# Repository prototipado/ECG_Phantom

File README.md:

# Fantoma ECG

Simulador y calibrador de señales electrocardíacas multicanal. Este proyecto integra el diseño de hardware analógico/digital, simulaciones de filtrado en LTSpice, implementaciones de firmware para RP2040 y RP2350, y software de control en Python.

## Arquitectura del sistema

```mermaid
flowchart TD
    subgraph HW["Hardware y Señal"]
        MCU["RP2040 / RP2350<br/>(Raspberry Pi Pico)"]
        FILT["Filtros Reconstrucción PWM/DAC<br/>(Simulados en LTSpice)"]
        OUT["Salida 9-12 Derivaciones ECG + PPG"]
        MCU --> FILT --> OUT
    end
    subgraph FW["Firmware"]
        FW1["01. Reproductor Clínico (Flash/PhysioNet)"]
        FW2["02. Modelo Conducción (VdP + FHN)"]
        FW3["03. Síntesis Gaussiana + PPG"]
        FW4["04. Multi-Modelo 4-en-1"]
        FW5["05. Simulador Marcapasos (Pacer)"]
    end
    FW -.->|Carga según aplicación| MCU
    subgraph SW["Software Host"]
        PY["ecg_gui.py (Python)"]
        PLOT["Monitoreo multicanal en tiempo real"]
        CFG["Configuración de parámetros"]
        PY --> PLOT
        PY --> CFG
    end
    MCU <== "Streaming Serie USB (Handshake binario / 2000 SPS)" ==> PY
```

## Estructura del repositorio

* [`hardware/`](./hardware/): Proyecto KiCad (`pico_ecg`), esquemáticos, PCB, huellas, modelos 3D, Gerber y BOM.
* [`simulaciones/`](./simulaciones/): Circuitos LTSpice para filtrado analógico (PWM a voltaje), detección de impulsos y scripts en Python.
* [`firmware/`](./firmware/): Código para Raspberry Pi Pico y Pico 2:
  * [`01_pico_ecg`](./firmware/01_pico_ecg/): Reproductor de registros clínicos guardados en memoria Flash.
  * [`02_pico_conduction_model`](./firmware/02_pico_conduction_model/): Modelo biofísico de conducción cardíaca (Van der Pol + FitzHugh-Nagumo, 12 derivaciones).
  * [`03_pico_ecg_gaussian_ppg`](./firmware/03_pico_ecg_gaussian_ppg/): Síntesis analítica evento-driven (kernels Gaussianos) de ECG 12 derivaciones + pulso óptico PPG.
  * Módulos avanzados en desarrollo (`04_pico_multimodel` y `05_pace_sim_intracardiac_9_nodes`).
* [`software/`](./software/): Interfaz de escritorio en Python para visualización multicanal, registro de datos y control remoto.
* [`datasets/`](./datasets/): Registros de bases clínicas (PhysioNet, LUDB) y scripts para convertirlos a arreglos en C (`.h`).
* [`docs/`](./docs/): Protocolo de comunicación, referencias bibliográficas y notas de diseño.

## Características

* Salida de derivaciones estándar (I, II, III, aVR, aVL, aVF, V1-V6) y canal auxiliar PPG.
* Generación analógica a electrodos y transmisión serie por USB (hasta 2000 SPS).
* Control local mediante menú en pantalla OLED y encoder rotativo, o remoto desde la GUI en Python.
* Simulación de ritmos normales y patologías (taquicardia, bradicardia, fibrilación, bloqueos AV, deriva de línea base).

## Inicio rápido

### Dependencias de software (GUI)

```bash
cd software
python -m venv .venv

# En Windows:
.venv\Scripts\activate

# En Linux/macOS:
source .venv/bin/activate

pip install -r requirements.txt
python ecg_gui.py
```

### Carga de firmware

1. Navegar a la carpeta del firmware deseado (por ejemplo, [`firmware/01_pico_ecg/`](./firmware/01_pico_ecg/)).
2. Conectar la Raspberry Pi Pico manteniendo presionado el botón BOOTSEL.
3. Copiar el archivo `.uf2` compilado a la unidad USB generada.

## Estado del desarrollo

- [x] Caracterización y simulación de filtros pasa-bajos en LTSpice.
- [x] Firmware base `01_pico_ecg` para reproducción de registros clínicos.
- [x] Firmware `02_pico_conduction_model` (modelo electrofisiológico VdP + FHN).
- [x] Firmware `03_pico_ecg_gaussian_ppg` (síntesis Gaussiana ECG de 12 derivaciones + pulso óptico PPG).
- [ ] Suite de firmwares avanzados (`04_pico_multimodel` y `05_pace_sim_intracardiac_9_nodes`).
- [x] Diseños finales de PCB y acondicionamiento de señal en KiCad.
- [x] GUI en Python para captura en tiempo real, registro a CSV y compilación a ejecutable.

## Licencia

Este proyecto está bajo la Licencia MIT. Ver el archivo [`LICENSE`](./LICENSE) para más detalles.

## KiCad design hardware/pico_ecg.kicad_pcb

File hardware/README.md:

# Diseño de Hardware (KiCad)

Este directorio contiene el diseño electrónico y mecánico del Fantoma ECG, organizado como un proyecto unificado en KiCad.

## Estructura del proyecto

### Archivos de diseño KiCad

- **`pico_ecg.kicad_pro`**: Archivo principal del proyecto KiCad.
- **`pico_ecg.kicad_sch`**: Esquema de circuito principal (etapa analógica, microcontrolador y conectores).
- **`filtros.kicad_sch`**: Sub-esquema de la etapa de filtrado analógico.
- **`pacemaker.kicad_sch`**: Sub-esquema del simulador de marcapasos.
- **`pico_ecg.kicad_pcb`**: Ruteo de la placa de circuito impreso (PCB).

### Directorios

- **`pico_ecg.pretty/`**: Librería de huellas (footprints) locales utilizadas en el diseño — incluye huellas para OLED, Raspberry Pi Pico, cargador TP4056, encoder rotativo, entre otros.
- **`3d_models/`**: Modelos 3D de componentes (STEP/WRL) para visualización en KiCad — incluye Raspberry Pi Pico, OLED 0.96", cargador LiPo, encoder rotativo, y el ensamblaje completo (`pico_ecg.step`).
- **`case/`**: Archivos STL para impresión 3D del gabinete del dispositivo (`base.stl`, `frente.stl`) y fotografías del ensamblaje.
- **`gerber/`**: Archivos de fabricación (Gerber) y de perforación (Drill) listos para enviar a fabricación.
- **`bom/`**: Lista de materiales (`pico_ecg_BOM.csv`) con referencias de componentes, valores y huellas.
- **`docs/`**: Esquemático exportado en PDF (`pico_ecg.pdf`) para revisión rápida sin necesidad de KiCad.
- **`images/`**: Renderizados de la PCB y esquemas de filtrado.

## Imágenes

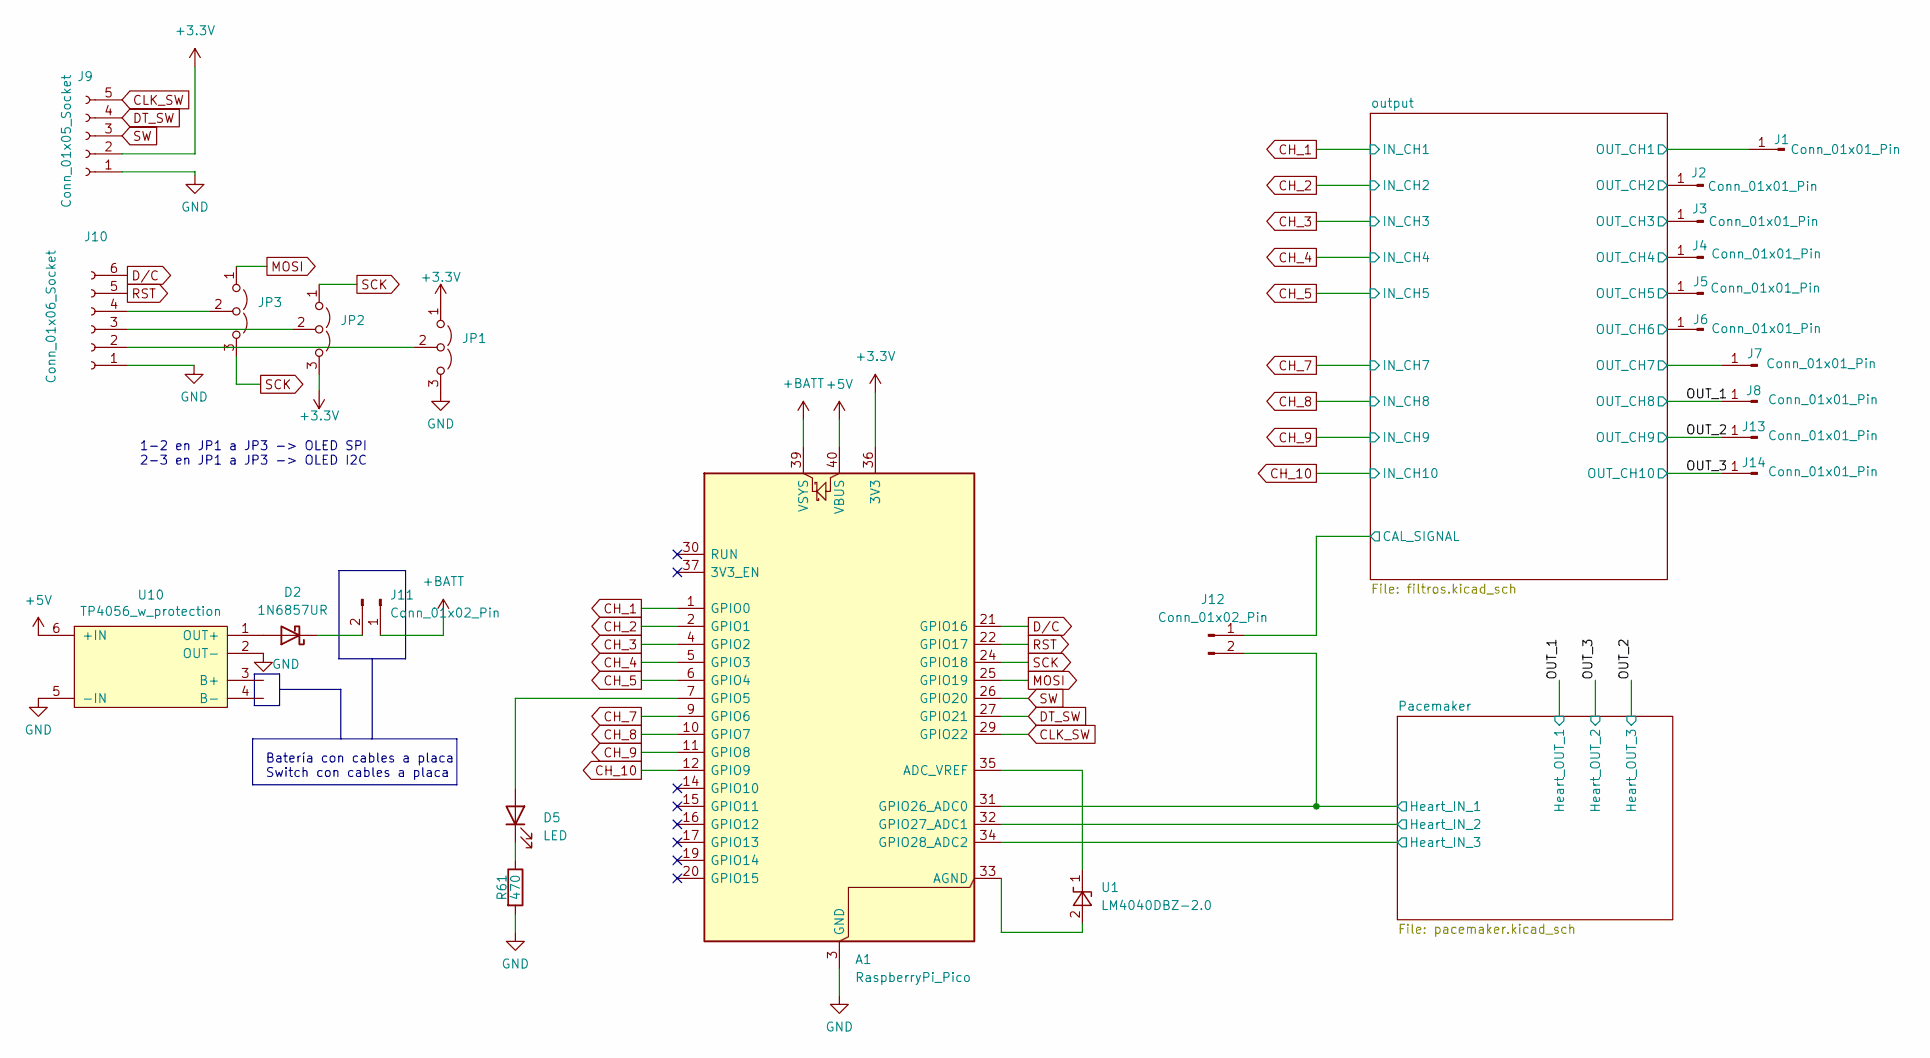
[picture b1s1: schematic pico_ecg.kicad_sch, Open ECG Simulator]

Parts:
A1: RaspberryPi_Pico; RaspberryPi_Pico_Common_Unspecified; Manufacturer PN SC1631
D2: 1N6857UR; D_MELF
D5: LED; LED_0805_2012Metric; Manufacturer PN 160-1427-1-ND
J1, J2, J3, J4, J5, J6, J7, J8, J13, J14: Conn_01x01_Pin; Pin_D1.4mm_L8.5mm_W2.8mm_FlatFork
J9: Conn_01x05_Socket; PinSocket_1x05_P2.54mm_Vertical
J10: Conn_01x06_Socket; PinSocket_1x06_P2.54mm_Vertical
J11, J12: Conn_01x02_Pin; PinHeader_1x02_P2.54mm_Vertical
JP1, JP2, JP3: Jumper_3_Open; SolderJumper-3_P1.3mm_Open_RoundedPad1.0x1.5mm
R61: 470; R_0603_1608Metric_Pad0.98x0.95mm_HandSolder; Manufacturer PN RC0603JR-07470RL
U1: LM4040DBZ-2.0; SOT-23; Manufacturer PN LM4040CIM3-2.0/NOPB
U10: TP4056_w_protection

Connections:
+3.3V: A1.36 (3V3), J9.2, JP1.1 (A), JP2.3 (B); also elsewhere on the board
+5V: A1.40 (VBUS), U10.6 (+IN)
+BATT: A1.39 (VSYS), J11.1
/OUT_1: J8.1 (Pin_1_1); also elsewhere on the board
/OUT_2: J13.1 (Pin_1_1); also elsewhere on the board
/OUT_3: J14.1 (Pin_1_1); also elsewhere on the board
/Pacemaker/Heart_IN_1: A1.31 (GPIO26_ADC0), J12.2; also elsewhere on the board
/Pacemaker/Heart_IN_2: A1.32 (GPIO27_ADC1); also elsewhere on the board
/Pacemaker/Heart_IN_3: A1.34 (GPIO28_ADC2); also elsewhere on the board
/output/CAL_SIGNAL: J12.1; also elsewhere on the board
/output/OUT_CH1: J1.1 (Pin_1_1); also elsewhere on the board
/output/OUT_CH2: J2.1 (Pin_1_1); also elsewhere on the board
/output/OUT_CH3: J3.1 (Pin_1_1); also elsewhere on the board
/output/OUT_CH4: J4.1 (Pin_1_1); also elsewhere on the board
/output/OUT_CH5: J5.1 (Pin_1_1); also elsewhere on the board
/output/OUT_CH6: J6.1 (Pin_1_1); also elsewhere on the board
/output/OUT_CH7: J7.1 (Pin_1_1); also elsewhere on the board
CH_1: A1.1 (GPIO0); also elsewhere on the board
CH_2: A1.2 (GPIO1); also elsewhere on the board
CH_3: A1.4 (GPIO2); also elsewhere on the board
CH_4: A1.5 (GPIO3); also elsewhere on the board
CH_5: A1.6 (GPIO4); also elsewhere on the board
CH_7: A1.9 (GPIO6); also elsewhere on the board
CH_8: A1.10 (GPIO7); also elsewhere on the board
CH_9: A1.11 (GPIO8); also elsewhere on the board
CH_10: A1.12 (GPIO9); also elsewhere on the board
CLK_SW: A1.29 (GPIO22), J9.5
DT_SW: A1.27 (GPIO21), J9.4
D/C: A1.21 (GPIO16), J10.6
GND: A1.3 (GND), A1.8 (GND), A1.13 (GND), A1.18 (GND), A1.23 (GND), A1.28 (GND), A1.38 (GND), J9.1, J10.1, JP1.3 (B), R61.2, U10.2 (OUT-), U10.5 (-IN); also elsewhere on the board
MOSI: A1.25 (GPIO19), JP3.1 (A)
unnamed: A1.35 (ADC_VREF), U1.1 (K)
unnamed: A1.33 (AGND), U1.2 (A)
unnamed: A1.7 (GPIO5), D5.2 (A)
unnamed: D2.2 (A), U10.1 (OUT+)
unnamed: D2.1 (K), J11.2
unnamed: D5.1 (K), R61.1
unnamed: J10.2, JP1.2 (C)
unnamed: J10.3, JP2.2 (C)
unnamed: J10.4, JP3.2 (C)
RST: A1.22 (GPIO17), J10.5
SCK: A1.24 (GPIO18), JP2.1 (A), JP3.3 (B)
SW: A1.26 (GPIO20), J9.3

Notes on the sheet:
1-2 en JP1 a JP3 -> OLED SPI 2-3 en JP1 a JP3 -> OLED I2C
Batería con cables a placa Switch con cables a placa

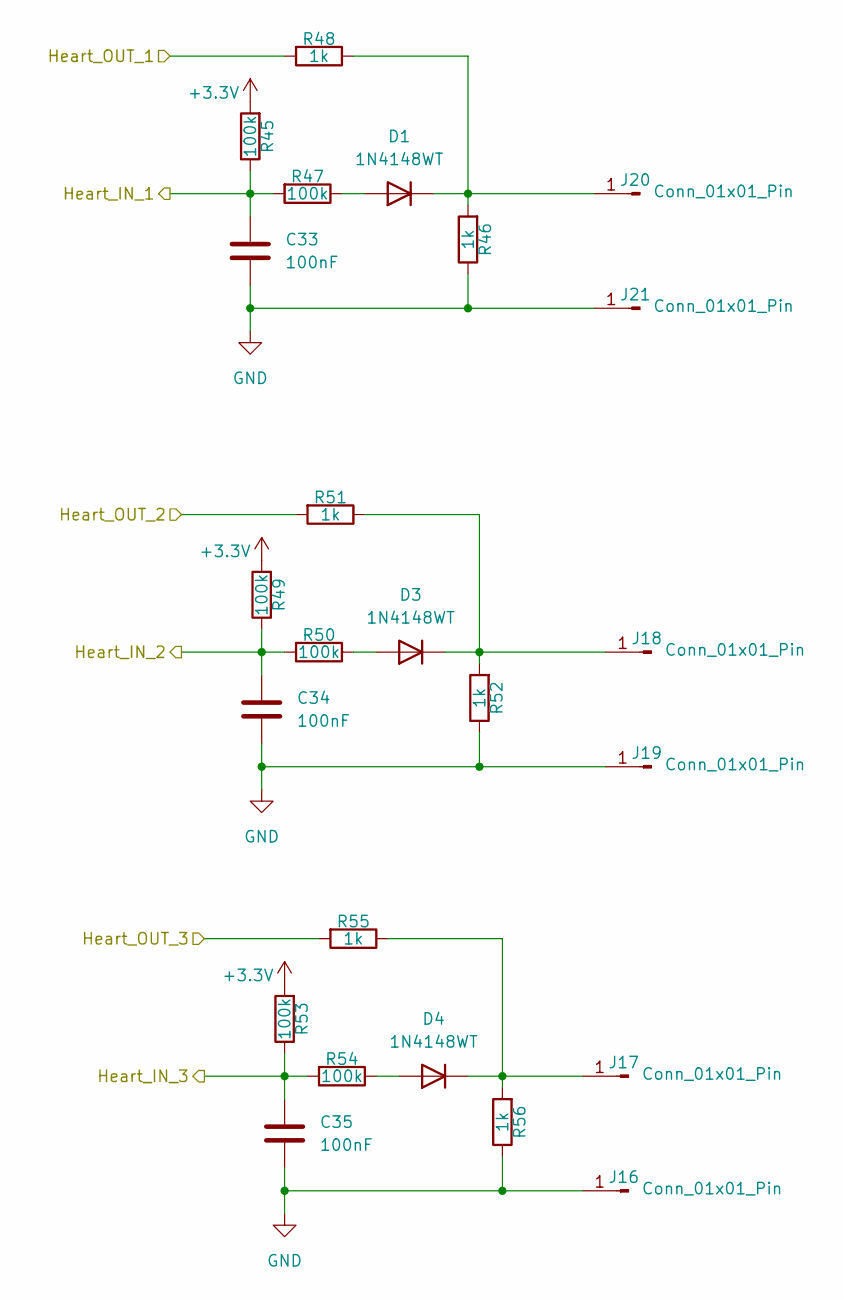
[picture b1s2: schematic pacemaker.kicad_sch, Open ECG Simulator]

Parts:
C33, C34, C35: 100nF; C_0603_1608Metric_Pad1.08x0.95mm_HandSolder; Manufacturer PN C0603C104K5RACTU
D1, D3, D4: 1N4148WT; D_SOD-523; Manufacturer PN 1N4148WT-7
J16, J17, J18, J19, J20, J21: Conn_01x01_Pin; Pin_D1.4mm_L8.5mm_W2.8mm_FlatFork
R45, R47, R49, R50, R53, R54: 100k; R_0603_1608Metric_Pad0.98x0.95mm_HandSolder; Manufacturer PN RC0603JR-07100KL
R46, R48, R51, R52, R55, R56: 1k; R_0603_1608Metric_Pad0.98x0.95mm_HandSolder; Manufacturer PN RC0603JR-071KL

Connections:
+3.3V: R45.2, R49.2, R53.2; also elsewhere on the board
/OUT_1: R48.2; also elsewhere on the board
/OUT_2: R55.2; also elsewhere on the board
/OUT_3: R51.2; also elsewhere on the board
/Pacemaker/Heart_IN_1: C33.2, R45.1, R47.2; also elsewhere on the board
/Pacemaker/Heart_IN_2: C34.2, R49.1, R50.2; also elsewhere on the board
/Pacemaker/Heart_IN_3: C35.2, R53.1, R54.2; also elsewhere on the board
GND: C33.1, C34.1, C35.1, J16.1 (Pin_1_1), J19.1 (Pin_1_1), J21.1 (Pin_1_1), R46.1, R52.1, R56.1; also elsewhere on the board
unnamed: D1.2 (A), R47.1
unnamed: D1.1 (K), J20.1 (Pin_1_1), R46.2, R48.1
unnamed: D3.2 (A), R50.1
unnamed: D3.1 (K), J18.1 (Pin_1_1), R51.1, R52.2
unnamed: D4.2 (A), R54.1
unnamed: D4.1 (K), J17.1 (Pin_1_1), R55.1, R56.2

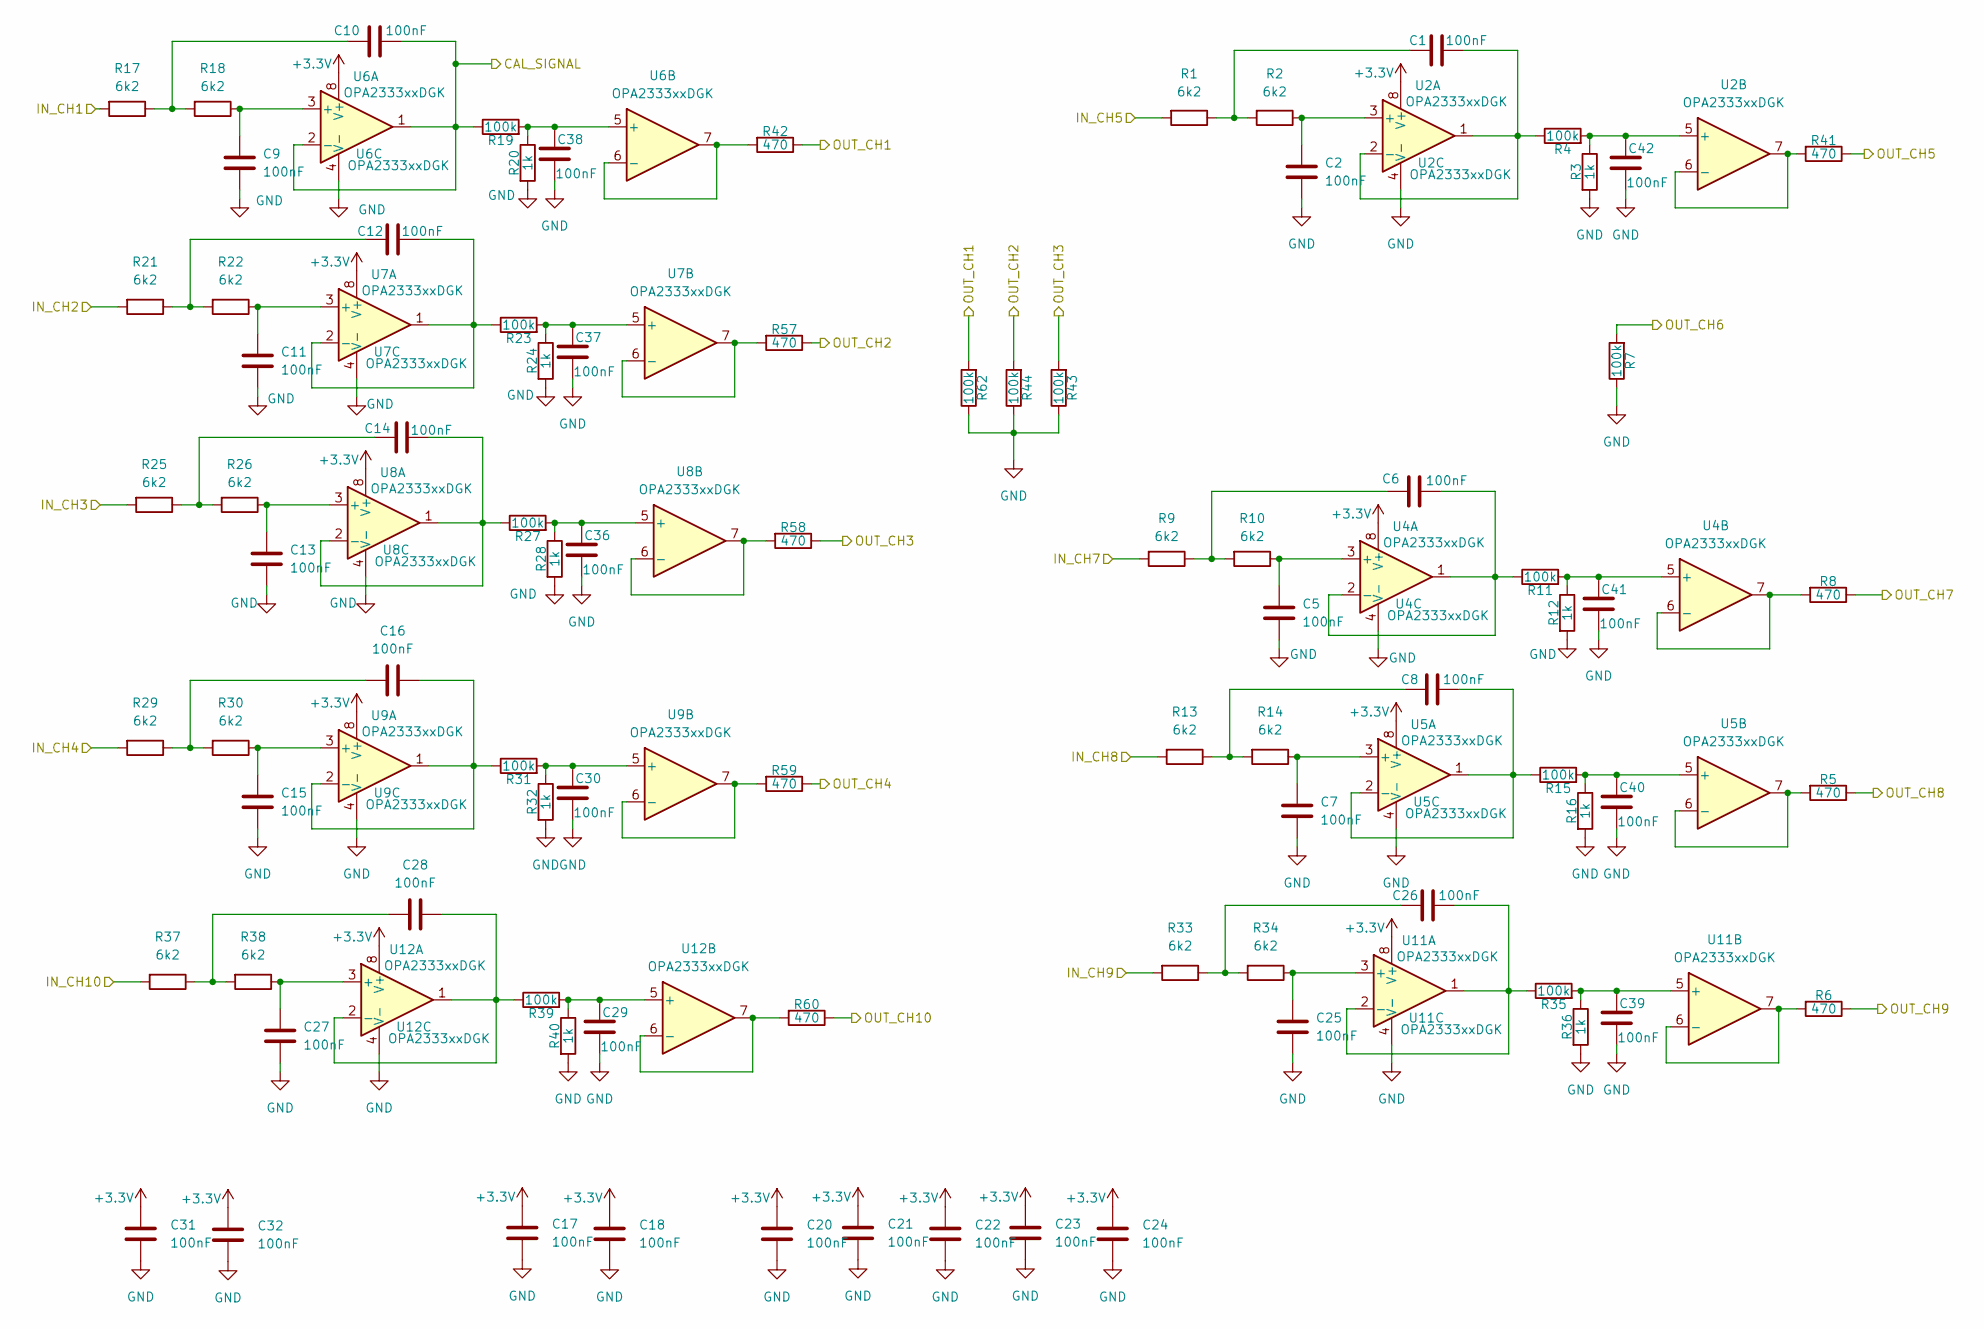
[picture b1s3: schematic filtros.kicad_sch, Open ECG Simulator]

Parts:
C1, C2, C5, C6, C7, C8, C9, C10, C11, C12, C13, C14, C15, C16, C17, C18, C20, C21, C22, C23, C24, C25, C26, C27, C28, C29, C30, C31, C32, C36, C37, C38, C39, C40, C41, C42: 100nF; C_0603_1608Metric_Pad1.08x0.95mm_HandSolder; Manufacturer PN C0603C104K5RACTU
R1, R2, R9, R10, R13, R14, R17, R18, R21, R22, R25, R26, R29, R30, R33, R34, R37, R38: 6k2; R_0603_1608Metric_Pad0.98x0.95mm_HandSolder; Manufacturer PN RC0603JR-076K2L
R3, R12, R16, R20, R24, R28, R32, R36, R40: 1k; R_0603_1608Metric_Pad0.98x0.95mm_HandSolder; Manufacturer PN RC0603JR-071KL
R4, R7, R11, R15, R19, R23, R27, R31, R35, R39, R43, R44, R62: 100k; R_0603_1608Metric_Pad0.98x0.95mm_HandSolder; Manufacturer PN RC0603JR-07100KL
R5, R6, R8, R41, R42, R57, R58, R59, R60: 470; R_0603_1608Metric_Pad0.98x0.95mm_HandSolder; Manufacturer PN RC0603JR-07470RL
U2, U4, U5, U6, U7, U8, U9, U11, U12: OPA2333xxDGK; DGK8-L; Manufacturer PN OPA2333AIDGKR

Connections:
+3.3V: C17.2, C18.2, C20.2, C21.2, C22.2, C23.2, C24.2, C31.2, C32.2, U2.8 (V+), U4.8 (V+), U5.8 (V+), U6.8 (V+), U7.8 (V+), U8.8 (V+), U9.8 (V+), U11.8 (V+), U12.8 (V+); also elsewhere on the board
/OUT_1: R5.1; also elsewhere on the board
/OUT_2: R6.1; also elsewhere on the board
/OUT_3: R60.1; also elsewhere on the board
/output/CAL_SIGNAL: C10.2, R19.1, U6.1, U6.2 (-); also elsewhere on the board
/output/OUT_CH1: R42.1, R62.2; also elsewhere on the board
/output/OUT_CH2: R44.2, R57.1; also elsewhere on the board
/output/OUT_CH3: R43.2, R58.1; also elsewhere on the board
/output/OUT_CH4: R59.1; also elsewhere on the board
/output/OUT_CH5: R41.1; also elsewhere on the board
/output/OUT_CH6: R7.2; also elsewhere on the board
/output/OUT_CH7: R8.1; also elsewhere on the board
CH_1: R17.2; also elsewhere on the board
CH_2: R21.2; also elsewhere on the board
CH_3: R25.2; also elsewhere on the board
CH_4: R29.2; also elsewhere on the board
CH_5: R1.2; also elsewhere on the board
CH_7: R9.2; also elsewhere on the board
CH_8: R13.2; also elsewhere on the board
CH_9: R33.2; also elsewhere on the board
CH_10: R37.2; also elsewhere on the board
GND: C2.2, C5.2, C7.2, C9.2, C11.2, C13.2, C15.2, C17.1, C18.1, C20.1, C21.1, C22.1, C23.1, C24.1, C25.2, C27.2, C29.1, C30.1, C31.1, C32.1, C36.1, C37.1, C38.1, C39.1, C40.1, C41.1, C42.1, R3.2, R7.1, R12.2, R16.2, R20.2, R24.2, R28.2, R32.2, R36.2, R40.2, R43.1, R44.1, R62.1, U2.4 (V-), U4.4 (V-), U5.4 (V-), U6.4 (V-), U7.4 (V-), U8.4 (V-), U9.4 (V-), U11.4 (V-), U12.4 (V-); also elsewhere on the board
unnamed: C1.1, R1.1, R2.2
unnamed: C6.1, R9.1, R10.2
unnamed: C8.1, R13.1, R14.2
unnamed: C10.1, R17.1, R18.2
unnamed: C12.1, R21.1, R22.2
unnamed: C14.1, R25.1, R26.2
unnamed: C16.1, R29.1, R30.2
unnamed: C26.1, R33.1, R34.2
unnamed: C28.1, R37.1, R38.2
unnamed: C2.1, R2.1, U2.3 (+)
unnamed: C1.2, R4.1, U2.1, U2.2 (-)
unnamed: C42.2, R3.1, R4.2, U2.5 (+)
unnamed: R41.2, U2.6 (-), U2.7
unnamed: C5.1, R10.1, U4.3 (+)
unnamed: C6.2, R11.1, U4.1, U4.2 (-)
unnamed: C41.2, R11.2, R12.1, U4.5 (+)
unnamed: R8.2, U4.6 (-), U4.7
unnamed: C7.1, R14.1, U5.3 (+)
unnamed: C8.2, R15.1, U5.1, U5.2 (-)
unnamed: C40.2, R15.2, R16.1, U5.5 (+)
unnamed: R5.2, U5.6 (-), U5.7
unnamed: C9.1, R18.1, U6.3 (+)
unnamed: C38.2, R19.2, R20.1, U6.5 (+)
unnamed: R42.2, U6.6 (-), U6.7
unnamed: C11.1, R22.1, U7.3 (+)
unnamed: C12.2, R23.1, U7.1, U7.2 (-)
unnamed: C37.2, R23.2, R24.1, U7.5 (+)
unnamed: R57.2, U7.6 (-), U7.7
unnamed: C13.1, R26.1, U8.3 (+)
unnamed: C14.2, R27.1, U8.1, U8.2 (-)
unnamed: C36.2, R27.2, R28.1, U8.5 (+)
unnamed: R58.2, U8.6 (-), U8.7
unnamed: C15.1, R30.1, U9.3 (+)
unnamed: C16.2, R31.1, U9.1, U9.2 (-)
unnamed: C30.2, R31.2, R32.1, U9.5 (+)
unnamed: R59.2, U9.6 (-), U9.7
unnamed: C25.1, R34.1, U11.3 (+)
unnamed: C26.2, R35.1, U11.1, U11.2 (-)
unnamed: C39.2, R35.2, R36.1, U11.5 (+)
unnamed: R6.2, U11.6 (-), U11.7
unnamed: C27.1, R38.1, U12.3 (+)
unnamed: C28.2, R39.1, U12.1, U12.2 (-)
unnamed: C29.2, R39.2, R40.1, U12.5 (+)
unnamed: R60.2, U12.6 (-), U12.7

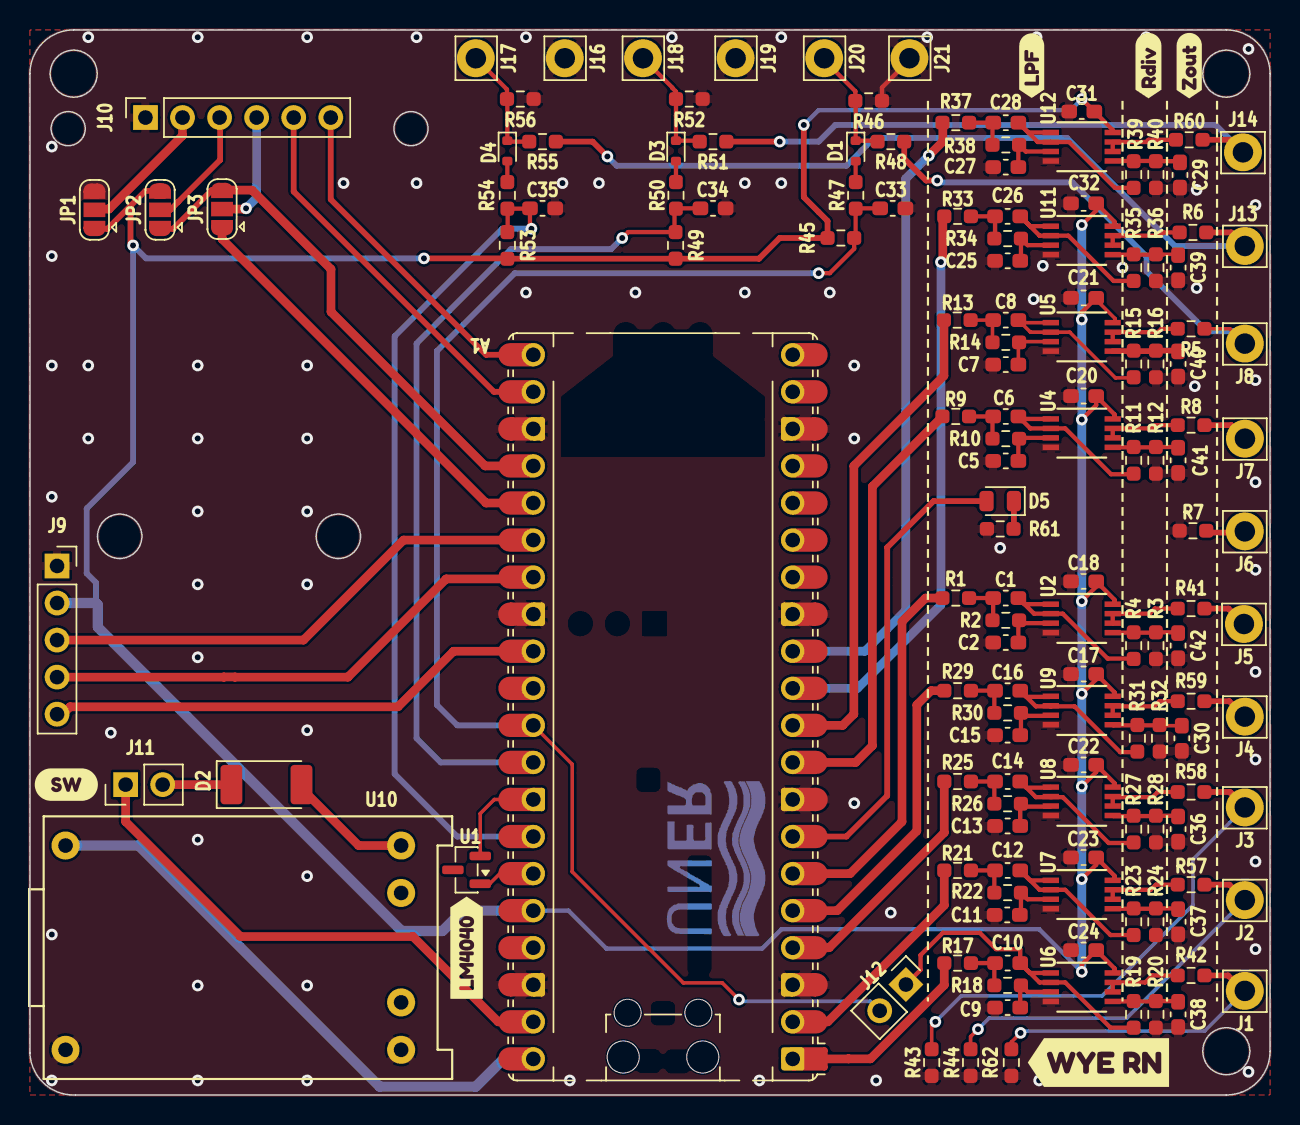
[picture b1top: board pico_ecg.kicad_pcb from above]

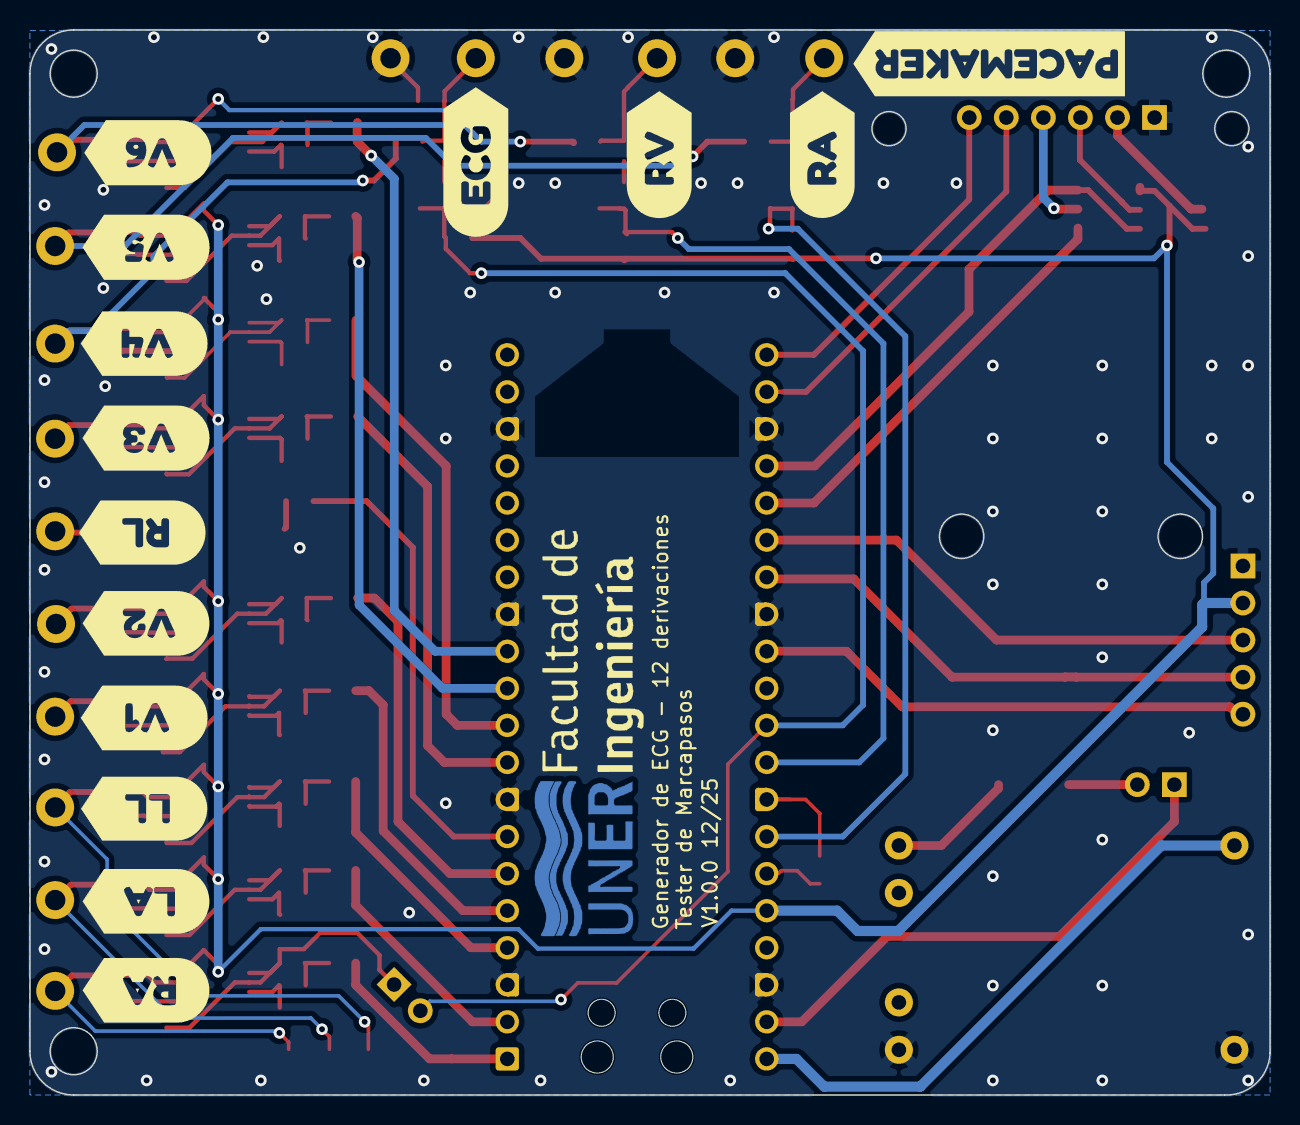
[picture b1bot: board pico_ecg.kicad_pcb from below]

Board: 2 copper layers, 85.0 x 73.0 mm, 161 parts (14 on the bottom side), 93 nets.

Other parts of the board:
kibuzzard-695407C8: G***; kibuzzard-695407C8
kibuzzard-695407DC: G***; kibuzzard-695407DC
kibuzzard-695407F6: G***; kibuzzard-695407F6
kibuzzard-695407FF: G***; kibuzzard-695407FF
kibuzzard-695409B2: G***; kibuzzard-695409B2
kibuzzard-695409D3: G***; kibuzzard-695409D3
kibuzzard-695409F9: G***; kibuzzard-695409F9
kibuzzard-6954080E: G***; kibuzzard-6954080E
kibuzzard-6954081B: G***; kibuzzard-6954081B
kibuzzard-6954082B: G***; kibuzzard-6954082B
kibuzzard-6954083E: G***; kibuzzard-6954083E
kibuzzard-6954084A: G***; kibuzzard-6954084A
kibuzzard-69540806: G***; kibuzzard-69540806
kibuzzard-69540813: G***; kibuzzard-69540813
kibuzzard-69540823: G***; kibuzzard-69540823
kibuzzard-69540831: G***; kibuzzard-69540831
kibuzzard-69540844: G***; kibuzzard-69540844
kibuzzard-69540856: G***; kibuzzard-69540856
kibuzzard-69540869: G***; kibuzzard-69540869
kibuzzard-69540875: G***; kibuzzard-69540875

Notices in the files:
README.md:
License: MIT
